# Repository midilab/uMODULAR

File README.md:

# uMODULAR

A collection of **hardware schematics**, **PCBs**, and **libraries** for **real-time embedded applications** in the field of music and video.

**Hardware:** Modules effortlessly combine to enhance and extend the capabilities of your device.  
**Firmware:** All the challenging and intricate aspects of real-time and concurrency in music or video applications are encapsulated within a safe and intuitive API via libraries.  

The framework provides multi-architecture support, allowing for seamless compilation across various microcontrollers without the need for manual adjustments or modifications. This ensures a streamlined development process and simplifies the programming and debugging tasks associated with real-time and concurrent operations.  

## Hardware

The physical modules are released under the CC-BY-SA 4.0 license and are available in Kicad format, providing electronic schematics and PCB designs for creating your own audio/video/sensorial device controller or signal processing box.  

## Protocol interfaces

The uMODULAR framework is meticulously designed to ensure seamless interoperability with a wide range of audio and video devices available on the market. Its compatibility extends to various protocols and standards, allowing integration with different devices.  
  
Avaliable Interfaces:  
  
**MIDI**  
OSC: **On roadmap**  
CV/GATE: **On roadmap**  
DMX: **On roadmap**  

## Libraries

The firmware libraries are built for the Arduino platform, with support for PlatformIO, and are compatible with various microcontroller architectures and boards, including classic AVRs and modern ARMs.  
  
**AVRs:** ATmega168, ATmega328, ATmega16u4, ATmega32u4 and ATmega2560.  
**ARMs:** ESP32, SAMD21 and All Teensy ARM microcontrollers.  
  
**Boards:** All AVR Arduino boards, All Teensy AVRs and ARMs, ESP32 based boards and Seedstudio XIAO M0.  
  
#### uCtrl

[uCtrl](https://github.com/midilab/uCtrl) is a comprehensive codebase library for the uMODULAR hardware project. It offers a driver layer for all uMODULAR modules and a user interface layer that simplifies the creation, extension, and sharing of advanced Arduino/PlatformIO applications.  
  
With uCtrl, you can achieve realtime-like functionality within the Arduino/PlatformIO ecosystem by leveraging hardware timer interruptions for precise task management. The library provides a resource-safe access through its API, ensuring efficient and reliable operation.  
  
Choose uCtrl for developing robust, portable, and high-performance musical instruments, sequencers, audio/video controllers, and other related machines on the Arduino/PlatformIO platform.  
  
#### uClock

[uClock](https://github.com/midilab/uClock) is a BPM-based Clock Generator Library provides a way to implement BPM clock tick calls using hardware interruption, ensuring the tightest and most accurate clock signal possible.  

## Applications

Real world applications using the uMODULAR framework:  

#### Aciduino V2

The project features a versatile step sequencer clone of Roland’s TB303/TR808, offering up to 16 tracks. It includes a comprehensive automation grid system for step, pattern, and mute control. The sequencer functions as a MIDI controller and incorporates an OLED display for visual feedback. Furthermore, the design is modular and allows for easy expansion with additional potentiometers, buttons, MIDI, or CV/Gate interfaces.  
  
You can download the app at [aciduino v2 repository](https://github.com/midilab/aciduino/tree/master/v2)  

## Oficial Website

You can find more informations about uMODULAR at http://midilab.co/umodular.

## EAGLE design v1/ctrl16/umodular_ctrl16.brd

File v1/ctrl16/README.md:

# ctrl16 module

ctrl16 is a 10cmx12.5cm PCB module for uMODULAR platform ready for 16 potentiometers plus 8 buttons/leds to make your device ready for controlling audio or video hardware/software stuffs.

## BOM list

### Buttons
**8x** Tactile Switches 6.0X4.3MM 160G <br />

### Leds
**8x** Through Hole Diffused T-1 (3 mm) <br />

### Potentiometers
**16x** 10K LINEAR 20%(Bourns PTV09A-4015F-B103) <br />

### ICs
**2x** CD4051BE <br />
**1x** 74HC595N <br />
**1x** 74HC165N <br />
**4x** Socket 16P DUAL WIPE <br />

### Ceramic Disc Capacitors 
**4x** 50V 100nf(.1uF) <br />

### Metal Film Resistors 1/4W Resistors
**8x** 220 <br />
**9x** 10k <br />

### Headers & Wire Housings 
**4x** 05+05 DIL VERTICAL PIN HEADER <br />

### Cable connection for uMODULAR base shield
**pick your size** Ribbon Cable 10 Conductors 28 AWG .050 <br />
**8x** Female Ribbon Cable Header 10 Position, 2 rows, 2.54 mm pitch <br />

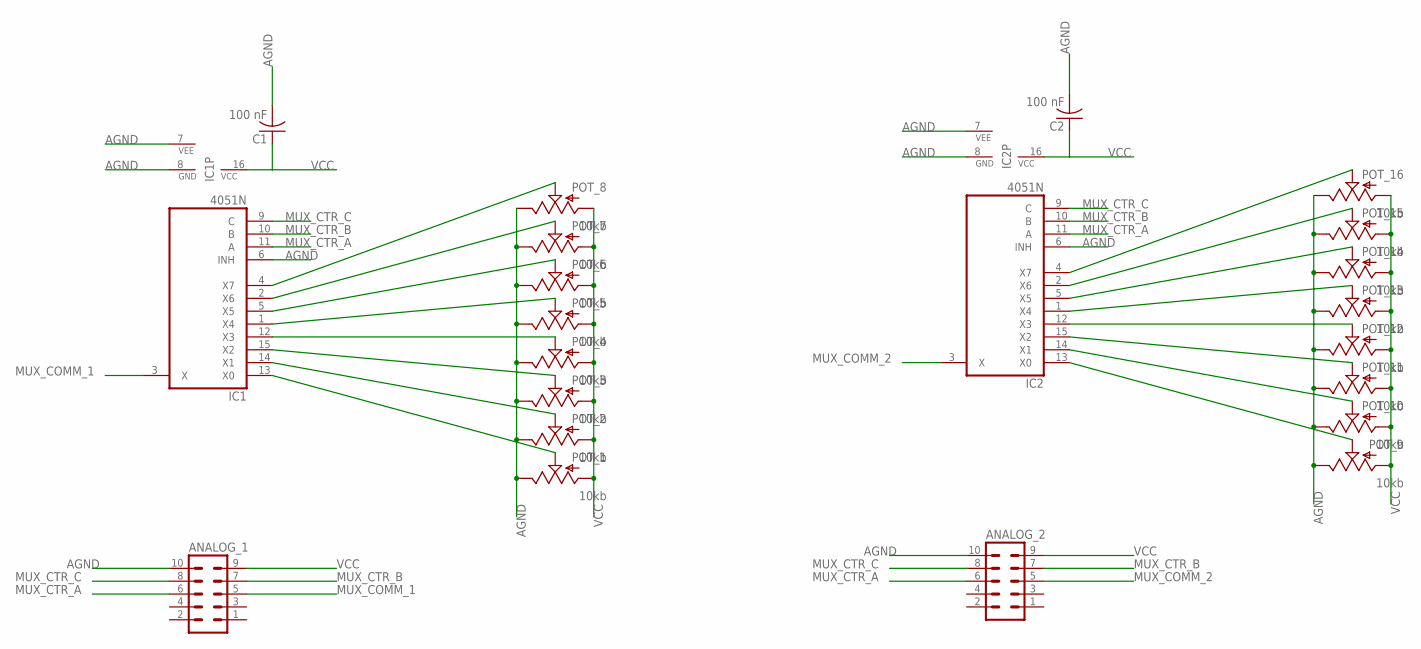
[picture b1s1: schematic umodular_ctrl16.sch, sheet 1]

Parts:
ANALOG_1, ANALOG_2: MA05-2
C1, C2: 100 nF; C050-024X044
IC1, IC2: 4051N; DIL16
POT_1, POT_2, POT_3, POT_4, POT_5, POT_6, POT_7, POT_8, POT_9, POT_10, POT_11, POT_12, POT_13, POT_14, POT_15, POT_16: 10kb; ALPS_POT

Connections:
AGND: ANALOG_1.10, ANALOG_2.10, C1.2, C2.2, IC1.6 (INH), IC1.7 (VEE), IC1.8 (GND), IC2.6 (INH), IC2.7 (VEE), IC2.8 (GND), POT_1.P$1 (E), POT_2.P$1 (E), POT_3.P$1 (E), POT_4.P$1 (E), POT_5.P$1 (E), POT_6.P$1 (E), POT_7.P$1 (E), POT_8.P$1 (E), POT_9.P$1 (E), POT_10.P$1 (E), POT_11.P$1 (E), POT_12.P$1 (E), POT_13.P$1 (E), POT_14.P$1 (E), POT_15.P$1 (E), POT_16.P$1 (E)
MUX_COMM_1: ANALOG_1.5, IC1.3 (X)
MUX_COMM_2: ANALOG_2.5, IC2.3 (X)
MUX_CTR_A: ANALOG_1.6, ANALOG_2.6, IC1.11 (A), IC2.11 (A)
MUX_CTR_B: ANALOG_1.7, ANALOG_2.7, IC1.10 (B), IC2.10 (B)
MUX_CTR_C: ANALOG_1.8, ANALOG_2.8, IC1.9 (C), IC2.9 (C)
unnamed: IC1.13 (X0), POT_1.P$2 (S)
unnamed: IC1.14 (X1), POT_2.P$2 (S)
unnamed: IC1.15 (X2), POT_3.P$2 (S)
unnamed: IC1.12 (X3), POT_4.P$2 (S)
unnamed: IC1.1 (X4), POT_5.P$2 (S)
unnamed: IC1.5 (X5), POT_6.P$2 (S)
unnamed: IC1.2 (X6), POT_7.P$2 (S)
unnamed: IC1.4 (X7), POT_8.P$2 (S)
unnamed: IC2.13 (X0), POT_9.P$2 (S)
unnamed: IC2.14 (X1), POT_10.P$2 (S)
unnamed: IC2.15 (X2), POT_11.P$2 (S)
unnamed: IC2.12 (X3), POT_12.P$2 (S)
unnamed: IC2.1 (X4), POT_13.P$2 (S)
unnamed: IC2.5 (X5), POT_14.P$2 (S)
unnamed: IC2.2 (X6), POT_15.P$2 (S)
unnamed: IC2.4 (X7), POT_16.P$2 (S)
VCC: ANALOG_1.9, ANALOG_2.9, C1.1, C2.1, IC1.16 (VCC), IC2.16 (VCC), POT_1.P$3 (A), POT_2.P$3 (A), POT_3.P$3 (A), POT_4.P$3 (A), POT_5.P$3 (A), POT_6.P$3 (A), POT_7.P$3 (A), POT_8.P$3 (A), POT_9.P$3 (A), POT_10.P$3 (A), POT_11.P$3 (A), POT_12.P$3 (A), POT_13.P$3 (A), POT_14.P$3 (A), POT_15.P$3 (A), POT_16.P$3 (A); also elsewhere on the board

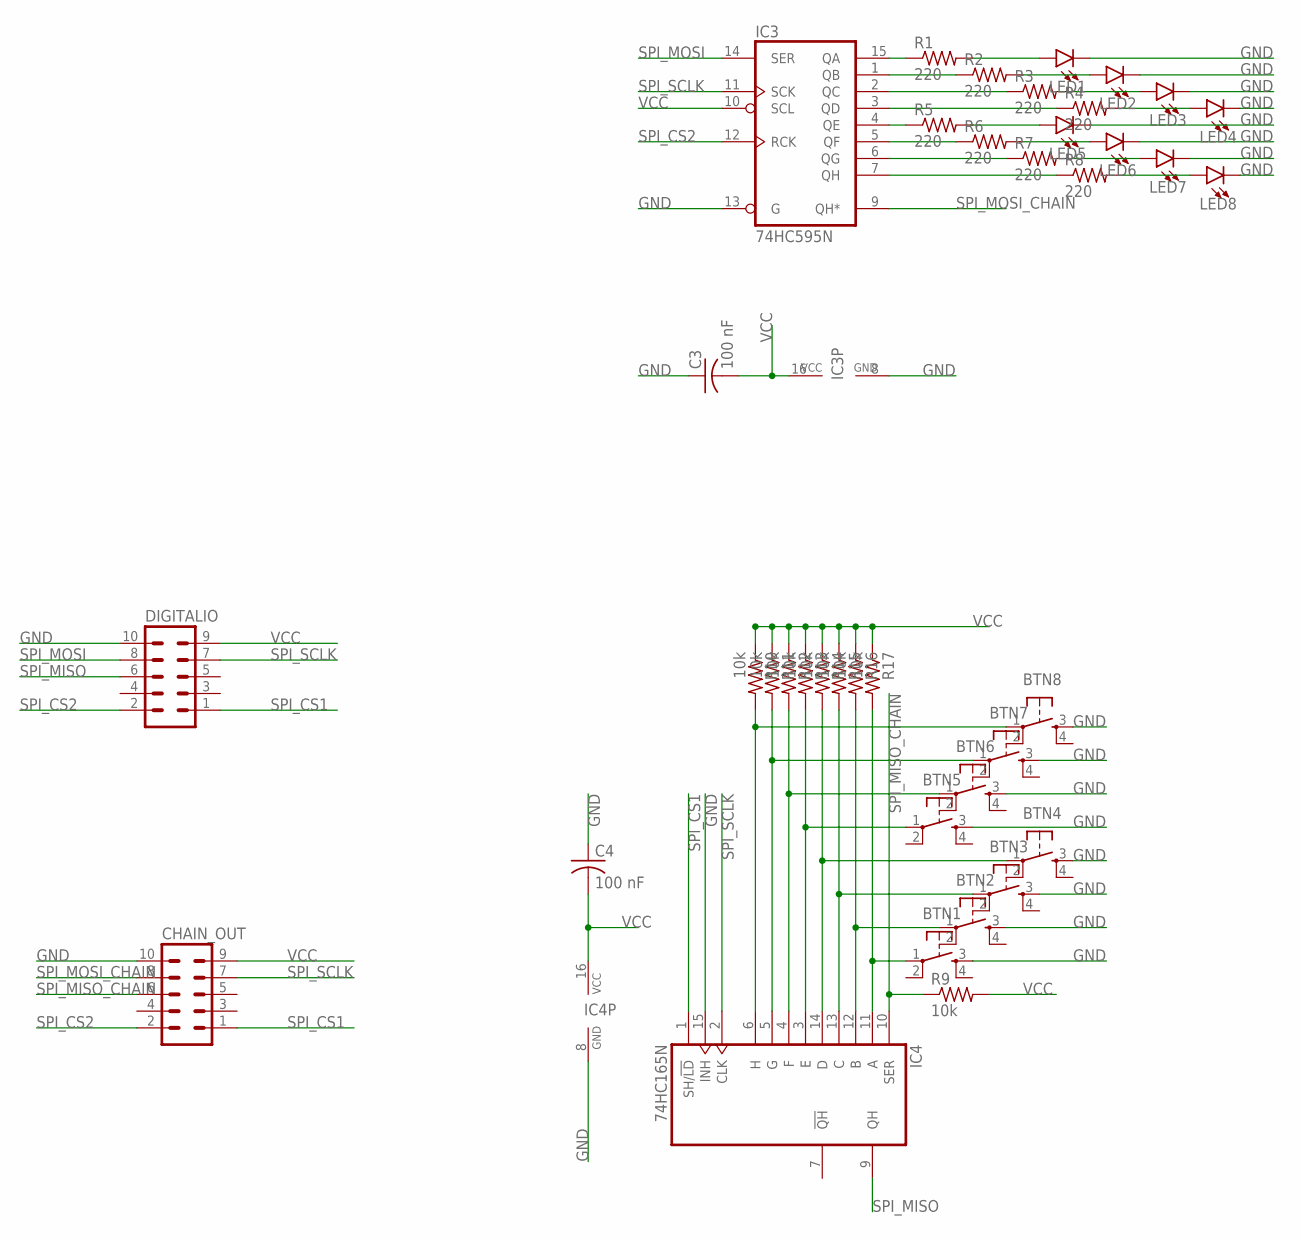
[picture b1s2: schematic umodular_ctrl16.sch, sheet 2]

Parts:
BTN1, BTN2, BTN3, BTN4, BTN5, BTN6, BTN7, BTN8: TAC_SWITCHPTH; TACTILE-PTH
C3, C4: 100 nF; C050-024X044
CHAIN_OUT: MA05-2
DIGITALIO: MA05-2
IC3: 74HC595N; DIL16
IC4: 74HC165N; DIL16
LED1, LED2, LED3, LED4, LED5, LED6, LED7, LED8: LED3MM; LED_3MM
R1, R2, R3, R4, R5, R6, R7, R8: 220; 0204/7
R9, R10, R11, R12, R13, R14, R15, R16, R17: 10k; 0204/7

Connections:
GND: BTN1.3, BTN2.3, BTN3.3, BTN4.3, BTN5.3, BTN6.3, BTN7.3, BTN8.3, C3.1, C4.1, CHAIN_OUT.10, DIGITALIO.10, IC3.8 (GND), IC3.13 (G), IC4.8 (GND), IC4.15 (INH), LED1.K (C), LED2.K (C), LED3.K (C), LED4.K (C), LED5.K (C), LED6.K (C), LED7.K (C), LED8.K (C)
unnamed: BTN1.1, IC4.11 (A), R17.2
unnamed: BTN2.1, IC4.12 (B), R16.2
unnamed: BTN3.1, IC4.13 (C), R15.2
unnamed: BTN4.1, IC4.14 (D), R14.2
unnamed: BTN5.1, IC4.3 (E), R13.2
unnamed: BTN6.1, IC4.4 (F), R12.2
unnamed: BTN7.1, IC4.5 (G), R11.2
unnamed: BTN8.1, IC4.6 (H), R10.2
unnamed: IC3.7 (QH), R8.1
unnamed: IC3.6 (QG), R7.1
unnamed: IC3.5 (QF), R6.1
unnamed: IC3.4 (QE), R5.1
unnamed: IC3.3 (QD), R4.1
unnamed: IC3.2 (QC), R3.1
unnamed: IC3.1 (QB), R2.1
unnamed: IC3.15 (QA), R1.1
unnamed: LED1.A, R1.2
unnamed: LED2.A, R2.2
unnamed: LED4.A, R4.2
unnamed: LED3.A, R3.2
unnamed: LED5.A, R5.2
unnamed: LED6.A, R6.2
unnamed: LED7.A, R7.2
unnamed: LED8.A, R8.2
SPI_CS1: CHAIN_OUT.1, DIGITALIO.1, IC4.1 (SH/!LD)
SPI_CS2: CHAIN_OUT.2, DIGITALIO.2, IC3.12 (RCK)
SPI_MISO: DIGITALIO.6, IC4.9 (QH)
SPI_MISO_CHAIN: CHAIN_OUT.6, IC4.10 (SER), R9.1
SPI_MOSI: DIGITALIO.8, IC3.14 (SER)
SPI_MOSI_CHAIN: CHAIN_OUT.8, IC3.9 (QH*)
SPI_SCLK: CHAIN_OUT.7, DIGITALIO.7, IC3.11 (SCK), IC4.2 (CLK)
VCC: C3.2, C4.2, CHAIN_OUT.9, DIGITALIO.9, IC3.10 (SCL), IC3.16 (VCC), IC4.16 (VCC), R9.2, R10.1, R11.1, R12.1, R13.1, R14.1, R15.1, R16.1, R17.1; also elsewhere on the board

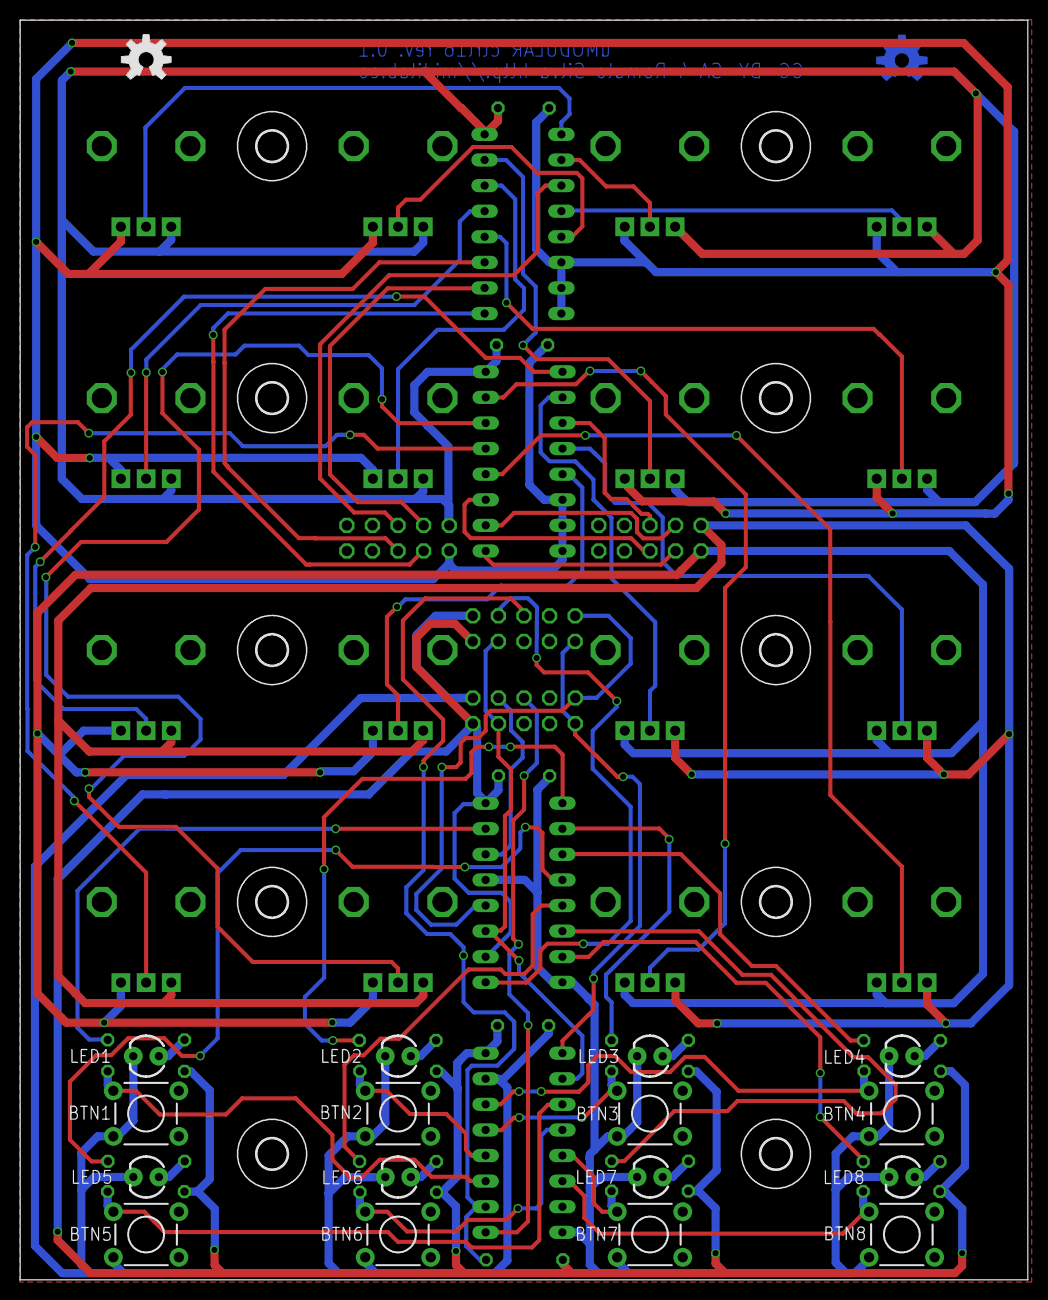
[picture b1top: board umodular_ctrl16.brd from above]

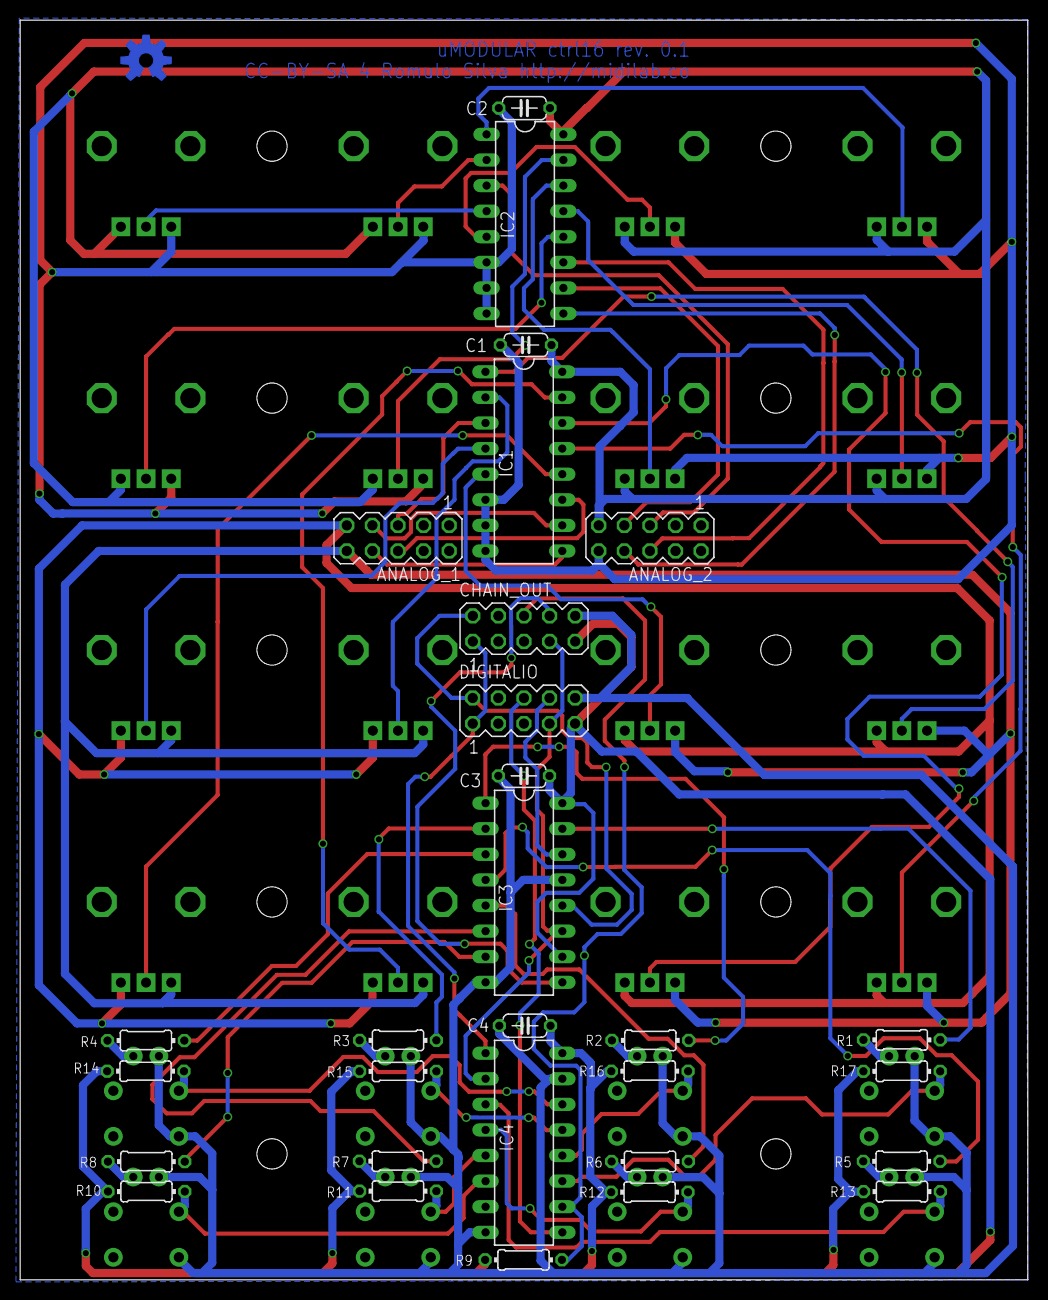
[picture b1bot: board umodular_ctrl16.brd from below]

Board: 2 copper layers, 100.0 x 125.0 mm, 73 parts (29 on the bottom side), 55 nets.

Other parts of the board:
U$1, U$2, U$3, U$4, U$5, U$6, U$8, U$11, U$12, U$13: 3,0
U$9, U$10: OSHW-LOGO-M

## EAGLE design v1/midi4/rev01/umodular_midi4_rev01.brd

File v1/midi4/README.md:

# midi4 module

midi4 is a 10cmx2.5cm PCB module for uMODULAR platform that supports 2 MIDI Ins and 2 MIDI Outs ports.

## BOM list

### MIDI Connector
**4x** Circular DIN Connectors 5P R/A PCB SHIELDED 5mm CIRC DIN RECPT <br />

### IC
**2x** 6N138 <br />
**2x** Socket 8P DUAL WIPE <br />

### Metal Film Resistors 1/4W Resistors
**2x** 4.7k <br />
**6x** 220 <br />
**2x** 1k <br />

### Diode
**2x** 1N4148 <br />

### Headers & Wire Housings
**1x** 05+05 DIL VERTICAL PIN HEADER <br />

### Cable connection for uMODULAR base shield
**pick your size** Ribbon Cable 10 Conductors 28 AWG .050 <br />
**2x** Female Ribbon Cable Header 10 Position, 2 rows, 2.54 mm pitch <br />

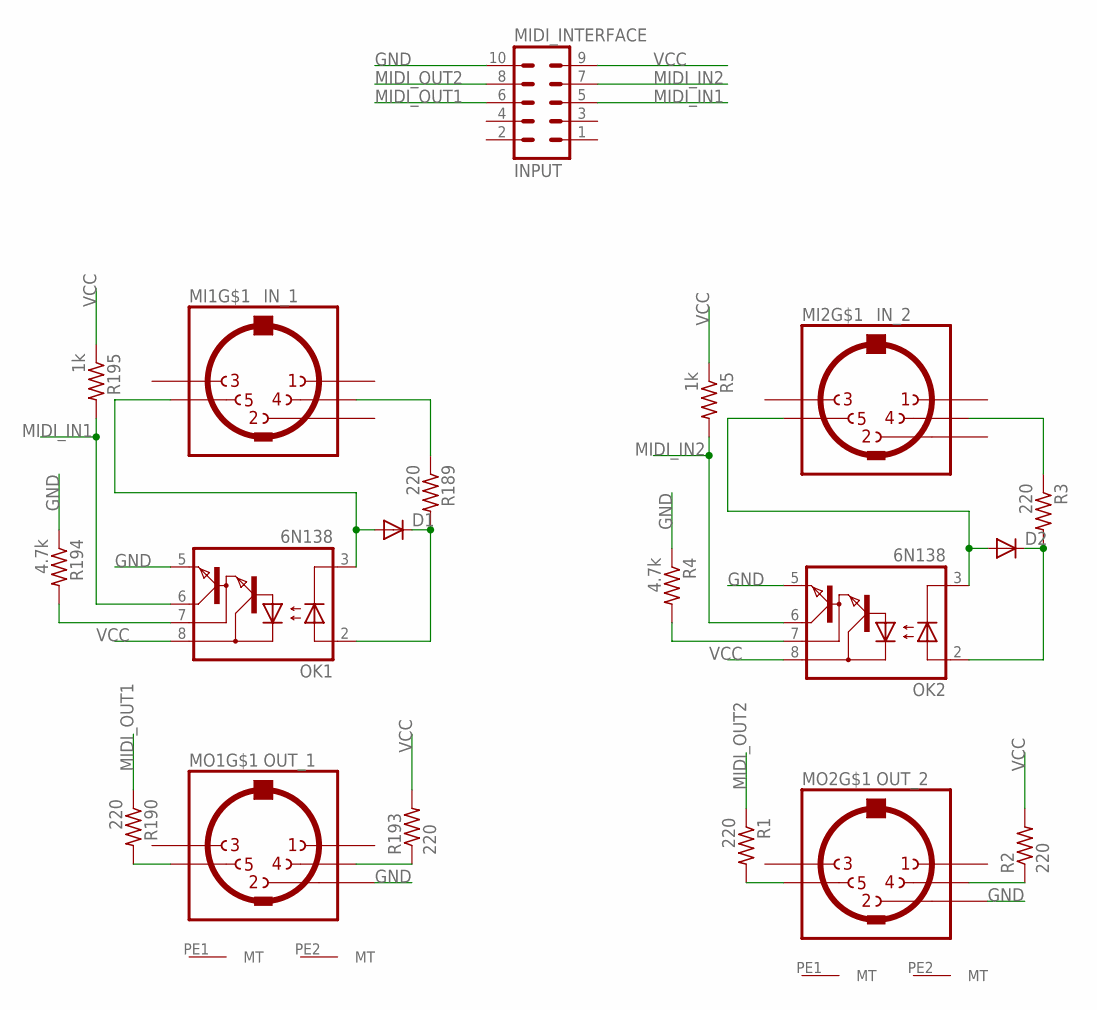
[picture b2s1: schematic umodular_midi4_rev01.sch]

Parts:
D1, D2: 1N4148DO35-7; DO35-7
MI1: IN_1; CP-2350
MI2: IN_2; CP-2350
MIDI_INTERFACE: INPUT; MA05-2
MO1: OUT_1; CP-2350
MO2: OUT_2; CP-2350
OK1, OK2: 6N138; DIL08
R1, R2, R3, R189, R190, R193: 220; 0204/7@1
R4, R194: 4.7k; 0204/7@1
R5, R195: 1k; 0204/7@1

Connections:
GND: MIDI_INTERFACE.10, MO1.2, MO2.2, OK1.5 (GND), OK2.5 (GND), R4.1, R194.1
MIDI_IN1: MIDI_INTERFACE.5, OK1.6 (VO), R195.2
MIDI_IN2: MIDI_INTERFACE.7, OK2.6 (VO), R5.2
MIDI_OUT1: MIDI_INTERFACE.6, R190.1
MIDI_OUT2: MIDI_INTERFACE.8, R1.1
unnamed: MO2.4, R2.1
unnamed: MO2.5, R1.2
unnamed: MI2.4, R3.1
unnamed: D2.C, OK2.2 (A), R3.2
unnamed: D2.A, MI2.5, OK2.3 (C)
unnamed: OK2.7 (VB), R4.2
unnamed: MI1.4, R189.1
unnamed: MO1.4, R193.1
unnamed: MO1.5, R190.2
unnamed: D1.C, OK1.2 (A), R189.2
unnamed: D1.A, MI1.5, OK1.3 (C)
unnamed: OK1.7 (VB), R194.2
VCC: MIDI_INTERFACE.9, OK1.8 (VCC), OK2.8 (VCC), R2.2, R5.1, R193.2, R195.1

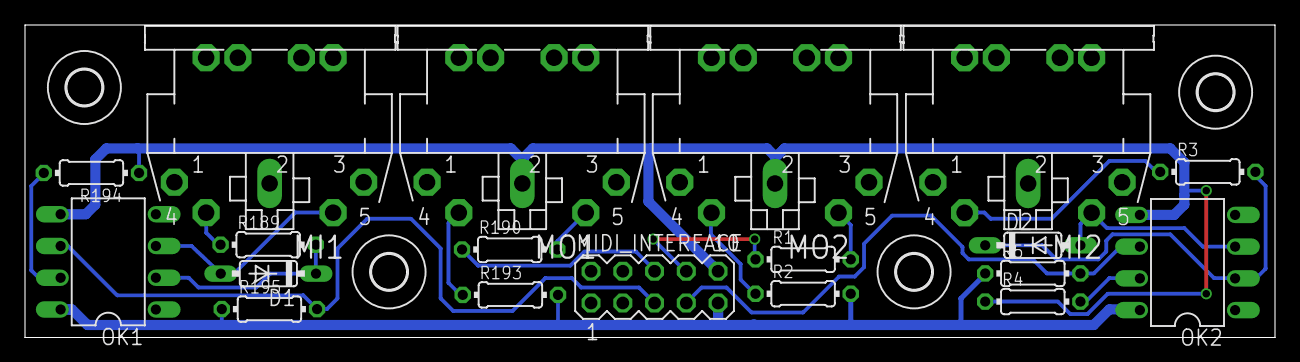
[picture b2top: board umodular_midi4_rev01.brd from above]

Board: 2 copper layers, 100.0 x 25.0 mm, 24 parts (0 on the bottom side), 18 nets.

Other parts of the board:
U$1, U$2, U$3, U$4: 2,8
U$5: OSHW-LOGO-M

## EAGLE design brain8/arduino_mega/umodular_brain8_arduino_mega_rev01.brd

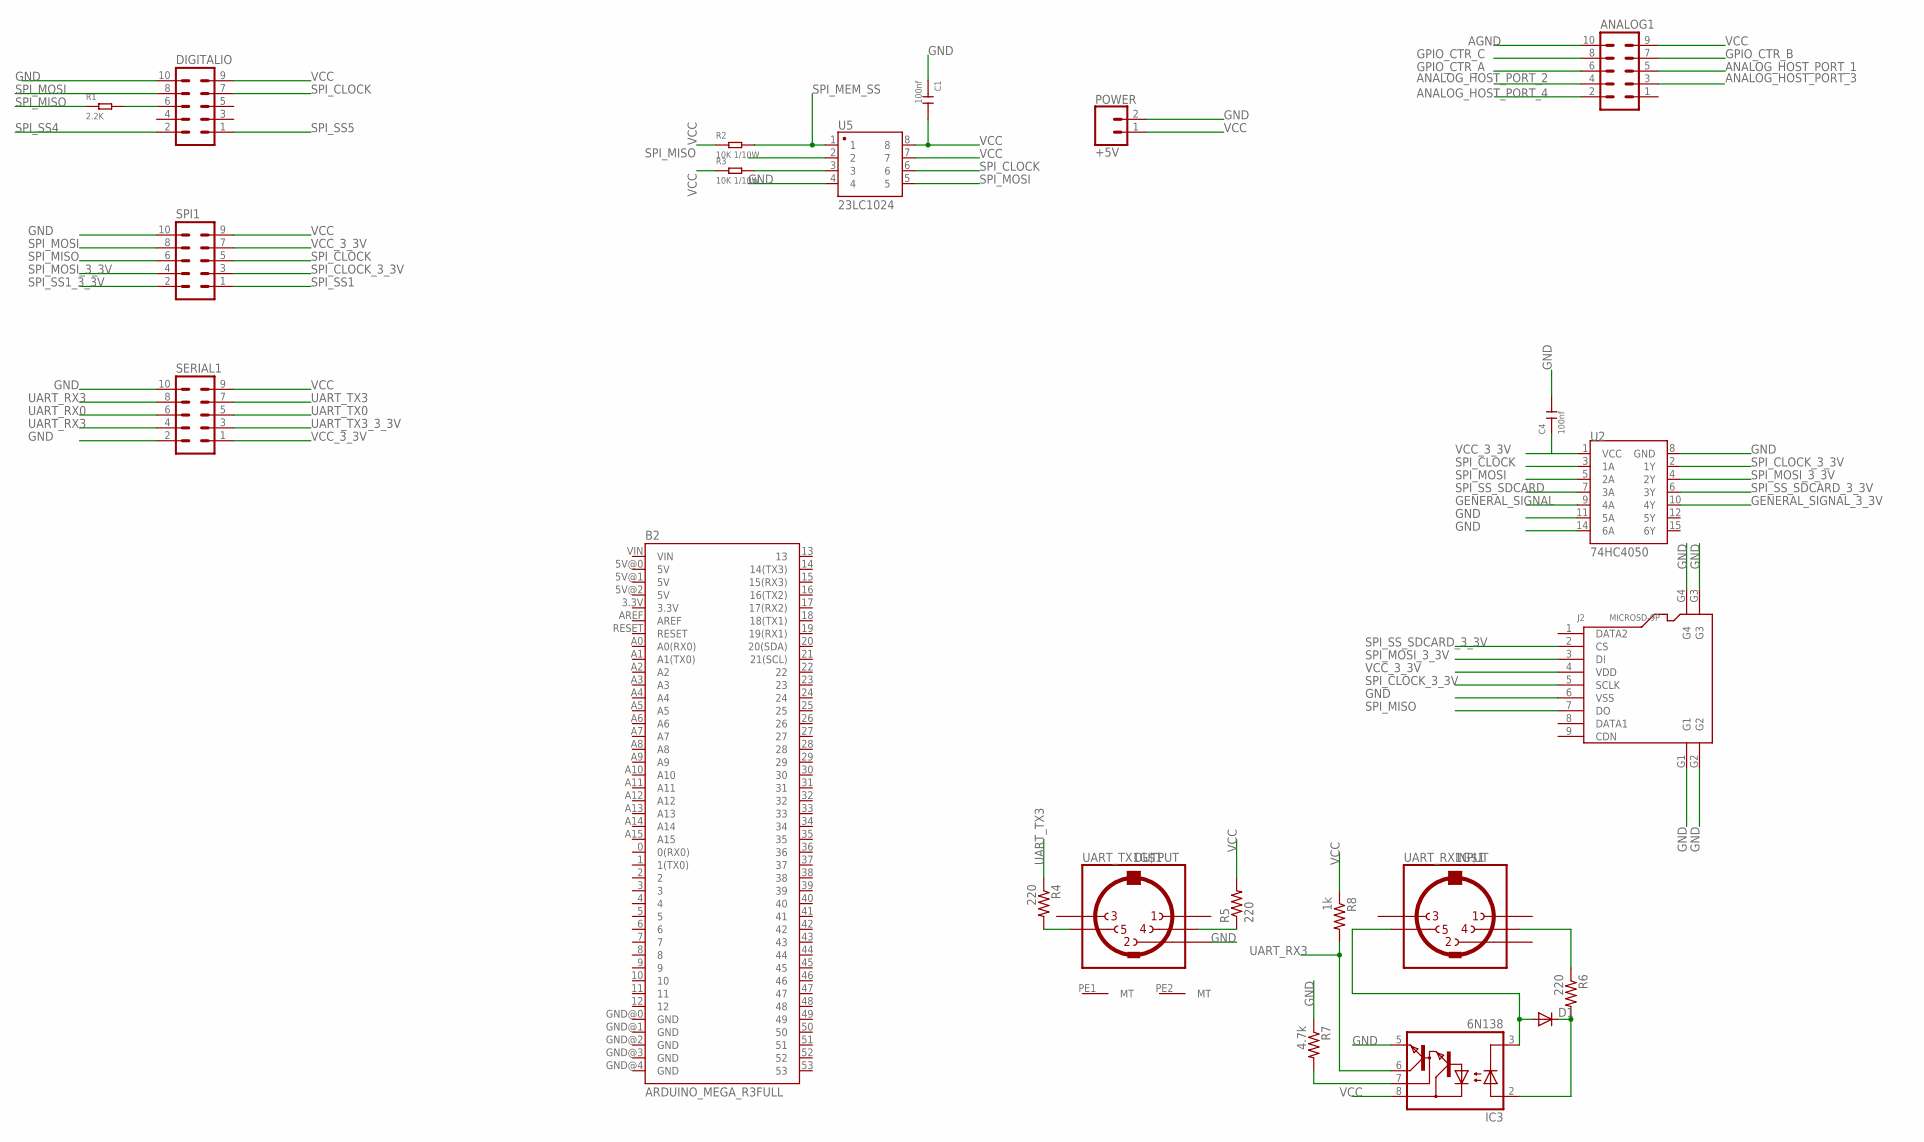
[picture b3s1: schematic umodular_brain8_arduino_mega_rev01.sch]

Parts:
ANALOG1: MA05-2
B2: ARDUINO_MEGA_R3FULL; ARDUINO_MEGA
C1, C4: 100nf; C0805
D1: 1N4148DO35-7; DO35-7
DIGITALIO: MA05-2
IC3: 6N138; DIL08
J2: MICROSD-9P; MICRO-SD9+4P-SMD-16.1X14.5X1.85MM
POWER: +5V; 1X02_LOCK_LONGPADS
R1: 2.2K; R0603
R2, R3: 10K 1/10W; R0603
R4, R5, R6: 220; 0204/7@1
R7: 4.7k; 0204/7@1
R8: 1k; 0204/7@1
SERIAL1: MA05-2
SPI1: MA05-2
U2: 74HC4050; SO16
U5: 23LC1024; SO08
UART_RX1: INPUT; CP-2350
UART_TX1: OUTPUT; CP-2350

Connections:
AGND: ANALOG1.10
ANALOG_HOST_PORT_1: ANALOG1.5
ANALOG_HOST_PORT_2: ANALOG1.4
ANALOG_HOST_PORT_3: ANALOG1.3
ANALOG_HOST_PORT_4: ANALOG1.2
GENERAL_SIGNAL: U2.9 (4A)
GENERAL_SIGNAL_3_3V: U2.10 (4Y)
GND: C1.1, C4.2, DIGITALIO.10, IC3.5 (GND), J2.6 (VSS), J2.G1, J2.G2, J2.G3, J2.G4, POWER.2, R7.1, SERIAL1.2, SERIAL1.10, SPI1.10, U2.8 (GND), U2.11 (5A), U2.14 (6A), U5.4, UART_TX1.2
GPIO_CTR_A: ANALOG1.6
GPIO_CTR_B: ANALOG1.7
GPIO_CTR_C: ANALOG1.8
unnamed: R5.1, UART_TX1.4
unnamed: R4.2, UART_TX1.5
unnamed: R3.2, U5.3
unnamed: R6.1, UART_RX1.4
unnamed: D1.C, IC3.2 (A), R6.2
unnamed: D1.A, IC3.3 (C), UART_RX1.5
unnamed: IC3.7 (VB), R7.2
unnamed: DIGITALIO.6, R1.2
SPI_CLOCK: DIGITALIO.7, SPI1.5, U2.3 (1A), U5.6
SPI_CLOCK_3_3V: J2.5 (SCLK), SPI1.3, U2.2 (1Y)
SPI_MEM_SS: R2.2, U5.1
SPI_MISO: J2.7 (DO), R1.1, SPI1.6, U5.2
SPI_MOSI: DIGITALIO.8, SPI1.8, U2.5 (2A), U5.5
SPI_MOSI_3_3V: J2.3 (DI), SPI1.4, U2.4 (2Y)
SPI_SS1: SPI1.1
SPI_SS1_3_3V: SPI1.2
SPI_SS4: DIGITALIO.2
SPI_SS5: DIGITALIO.1
SPI_SS_SDCARD: U2.7 (3A)
SPI_SS_SDCARD_3_3V: J2.2 (CS), U2.6 (3Y)
UART_RX0: SERIAL1.6
UART_RX3: IC3.6 (VO), R8.2, SERIAL1.4, SERIAL1.8
UART_TX0: SERIAL1.5
UART_TX3: R4.1, SERIAL1.7
UART_TX3_3_3V: SERIAL1.3
VCC: ANALOG1.9, C1.2, DIGITALIO.9, IC3.8 (VCC), POWER.1, R2.1, R3.1, R5.2, R8.1, SERIAL1.9, SPI1.9, U5.7, U5.8
VCC_3_3V: C4.1, J2.4 (VDD), SERIAL1.1, SPI1.7, U2.1 (VCC)

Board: 2 copper layers, 33 parts (3 on the bottom side), 20 nets, no tracks yet.

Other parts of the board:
U$1: OSHW-LOGO-M
U$2, U$3, U$4, U$6, U$7, U$8, U$9, U$10: OLED_0.96_I2C
U$5: OSHW-LOGO-L

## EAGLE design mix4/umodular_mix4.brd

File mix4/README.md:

# mix4 module

mix4 is a 10cmx12.5cm PCB module for uMODULAR platform ready for 4 faders and 4 potentiometers plus 8 buttons/leds to make your device ready for controlling audio or video hardware/software stuffs.

## BOM list

### Buttons
**8x** Tactile Switches 6.0X4.3MM 160G <br />

### Leds
**8x** Through Hole Diffused T-1 (3 mm) <br />

### Potentiometers
**4x** 10K LINEAR 20% (Bourns PTV09A-4015F-B103) <br />
**4x** Slide 15MM SHAFT NO DET 60MM STRK SNG LIN (Bourns PTA6043-2015DPB103) <br />

### ICs
**1x** CD4051BE <br />
**1x** 74HC595N <br />
**1x** 74HC165N <br />
**3x** Socket 16P DUAL WIPE <br />

### Ceramic Disc Capacitors
**3x** 50V 100nf(.1uF) <br />

### Metal Film Resistors 1/4W Resistors
**8x** 220 <br />
**9x** 10k <br />

### Headers & Wire Housings
**3x** 05+05 DIL VERTICAL PIN HEADER <br />

### Cable connection with uMODULAR base
**pick your size** Ribbon Cable 10 Conductors 28 AWG .050
**6x** Female Ribbon Cable Header 10 Position, 2 rows, 2.54 mm pitch

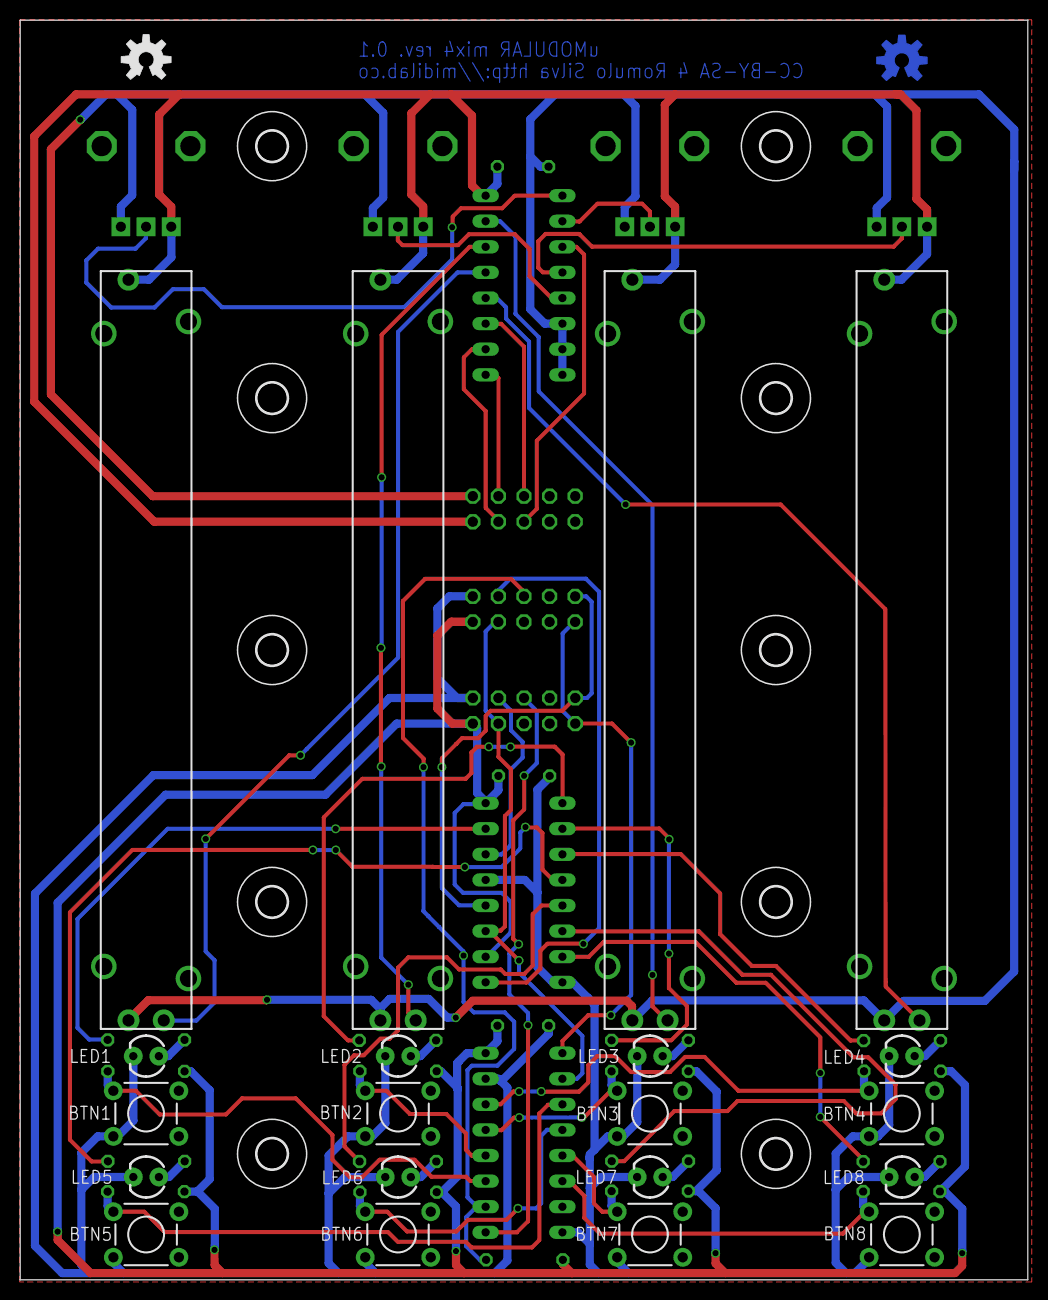
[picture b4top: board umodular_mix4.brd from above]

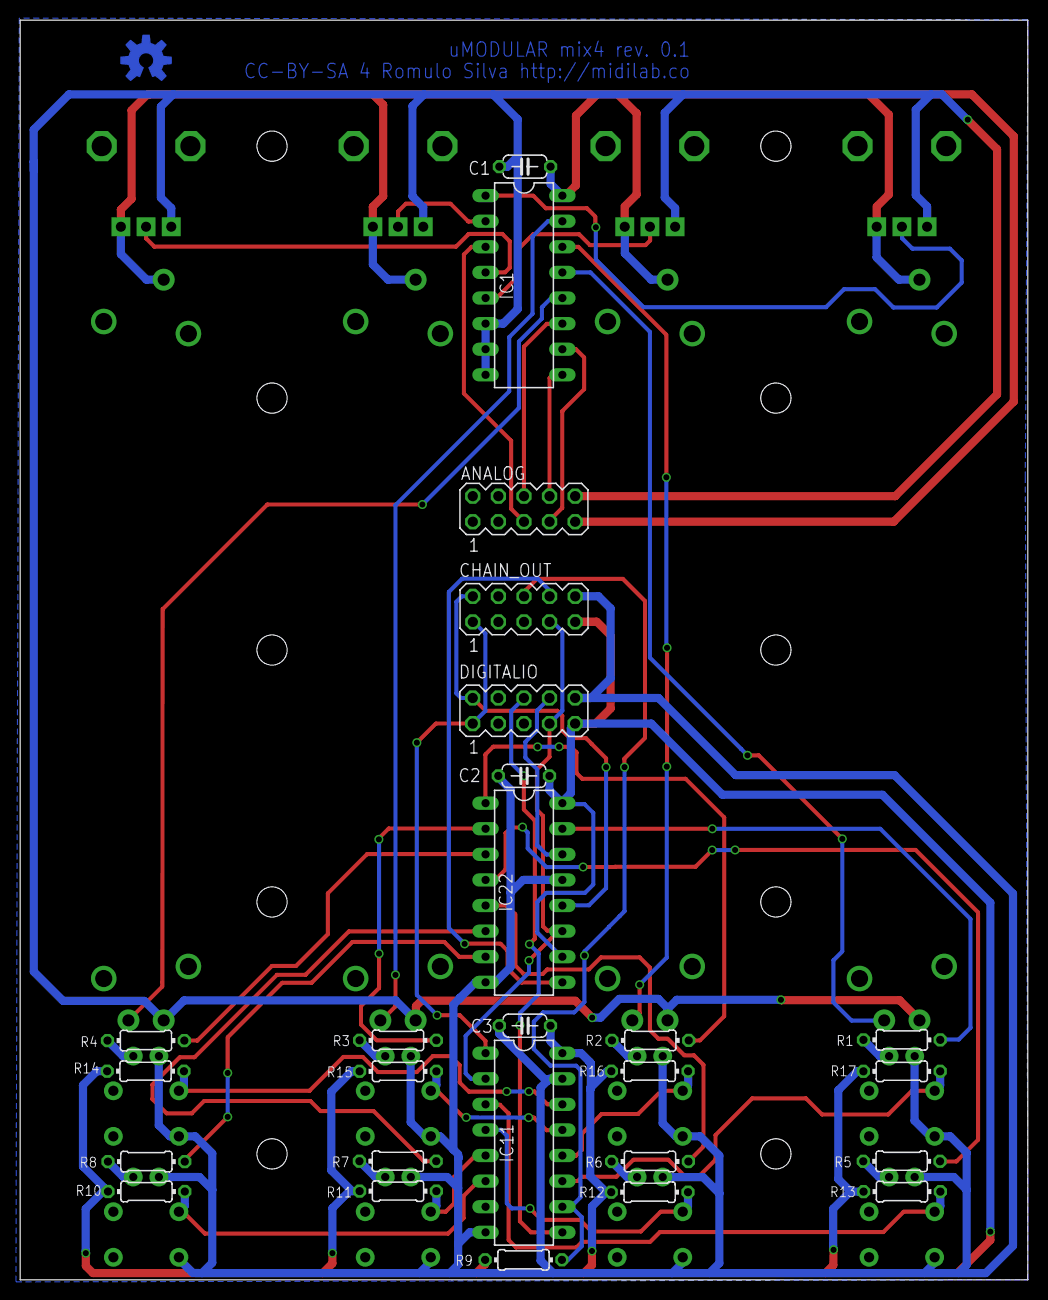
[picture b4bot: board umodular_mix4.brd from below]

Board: 2 copper layers, 100.0 x 125.0 mm, 62 parts (26 on the bottom side), 46 nets.

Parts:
ANALOG: MA05-2
BTN1, BTN2, BTN3, BTN4, BTN5, BTN6, BTN7, BTN8: TACTILE-PTH
C1, C2, C3: 100 nF; C050-024X044
CHAIN_OUT: MA05-2
DIGITALIO: MA05-2
FADER_1, FADER_2, FADER_3, FADER_4: 10kb; SLIDER
IC1: 4051N; DIL16
IC11: 74HC165N; DIL16
IC22: 74HC595N; DIL16
LED1, LED2, LED3, LED4, LED5, LED6, LED7, LED8: LED_3MM
POT_1, POT_2, POT_3, POT_4: 10kb; ALPS_POT
R1, R2, R3, R4, R5, R6, R7, R8: 220; 0204/7
R9, R10, R11, R12, R13, R14, R15, R16, R17: 10k; 0204/7
U$1, U$2, U$3, U$4, U$5, U$6, U$8, U$11, U$12, U$13: 3,0
U$9, U$10: OSHW-LOGO-M

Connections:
AGND: ANALOG.10, C1.2, FADER_1.1, FADER_2.1, FADER_3.1, FADER_4.1, IC1.6, IC1.7, IC1.8, POT_1.P$1, POT_2.P$1, POT_3.P$1, POT_4.P$1
GND: BTN1.3, BTN2.3, BTN3.3, BTN4.3, BTN5.3, BTN6.3, BTN7.3, BTN8.3, C2.1, C3.1, CHAIN_OUT.10, DIGITALIO.10, IC11.8, IC11.15, IC22.8, IC22.13, LED1.K, LED2.K, LED3.K, LED4.K, LED5.K, LED6.K, LED7.K, LED8.K
MUX_COMM: ANALOG.5, IC1.3
MUX_CTR_A: ANALOG.6, IC1.11
MUX_CTR_B: ANALOG.7, IC1.10
MUX_CTR_C: ANALOG.8, IC1.9
unnamed: BTN1.1, IC11.11, R17.2
unnamed: BTN2.1, IC11.12, R16.2
unnamed: BTN3.1, IC11.13, R15.2
unnamed: BTN4.1, IC11.14, R14.2
unnamed: BTN5.1, IC11.3, R13.2
unnamed: BTN6.1, IC11.4, R12.2
unnamed: BTN7.1, IC11.5, R11.2
unnamed: BTN8.1, IC11.6, R10.2
unnamed: IC22.7, R8.1
unnamed: IC22.6, R7.1
unnamed: IC22.5, R6.1
unnamed: IC22.4, R5.1
unnamed: IC22.3, R4.1
unnamed: IC22.2, R3.1
unnamed: IC22.1, R2.1
unnamed: IC22.15, R1.1
unnamed: LED1.A, R1.2
unnamed: LED2.A, R2.2
unnamed: LED4.A, R4.2
unnamed: LED3.A, R3.2
unnamed: LED5.A, R5.2
unnamed: LED6.A, R6.2
unnamed: LED7.A, R7.2
unnamed: LED8.A, R8.2
unnamed: FADER_1.2, IC1.13
unnamed: FADER_2.2, IC1.14
unnamed: FADER_3.2, IC1.15
unnamed: FADER_4.2, IC1.12
unnamed: IC1.1, POT_1.P$2
unnamed: IC1.5, POT_2.P$2
unnamed: IC1.2, POT_3.P$2
unnamed: IC1.4, POT_4.P$2
SPI_CS1: CHAIN_OUT.1, DIGITALIO.1, IC11.1
SPI_CS2: CHAIN_OUT.2, DIGITALIO.2, IC22.12
SPI_MISO: DIGITALIO.6, IC11.9
SPI_MISO_CHAIN: CHAIN_OUT.6, IC11.10, R9.1
SPI_MOSI: DIGITALIO.8, IC22.14
SPI_MOSI_CHAIN: CHAIN_OUT.8, IC22.9
SPI_SCLK: CHAIN_OUT.7, DIGITALIO.7, IC11.2, IC22.11
VCC: ANALOG.9, C1.1, C2.2, C3.2, CHAIN_OUT.9, DIGITALIO.9, FADER_1.3, FADER_2.3, FADER_3.3, FADER_4.3, IC1.16, IC11.16, IC22.10, IC22.16, POT_1.P$3, POT_2.P$3, POT_3.P$3, POT_4.P$3, R9.2, R10.1, R11.1, R12.1, R13.1, R14.1, R15.1, R16.1, R17.1

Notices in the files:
hardware/fader8/umodular_fader8.brd:
CC-BY-SA - Romulo Silva http://midilab.co
mix4/umodular_mix4.brd:
CC-BY-SA 4 Romulo Silva http://midilab.co
parts and their libraries:
SparkFun-Aesthetics: Licensing: CC v3.0 Share-Alike You are welcome to use this library for commercial purposes.
SparkFun-Connectors: Licensing: Creative Commons ShareAlike 4.0 International - https://creativecommons.org/licenses/by-sa/4.0
